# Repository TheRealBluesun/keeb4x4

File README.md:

# keeb4x4 v2

A 4×4 macropad: STM32G431, 16 MX-style keys with per-key SK6812
RGB, up to 12 Waveshare 0.85" ScreenKey display keycaps, an EC11 rotary
encoder, and a USB-C connection that streams key/encoder events to the host
as JSON. Firmware is Rust/Embassy, with a resident USB bootloader so you never
need a debug probe after the first flash.

## What's here

| Path | Contents |
| --- | --- |
| `keeb4x4.kicad_{pro,sch,pcb}` | KiCad project: schematic and 4-layer PCB (100 × 142.5 mm) |
| [`fab/`](fab/README.md) | Gerbers, BOM and CPL for JLCPCB, plus order settings and hand-solder list |
| [`FIRMWARE_NOTES.md`](FIRMWARE_NOTES.md) | Pin map, matrix polarity, encoder, LED chain — the hardware facts firmware relies on |
| [`firmware/`](firmware/README.md) | Rust/Embassy application firmware |
| [`bootloader/`](bootloader/README.md) | USB DFU bootloader, recovery, memory layout |
| [`host/`](host/README.md) | `keeb` CLI: list devices, listen to events, build and flash firmware |
| [`enclosure/`](enclosure/README.md) | 3D-printable base (STL/STEP) and its parametric source |
| [`docs/PARTS.md`](docs/PARTS.md) | What to buy beyond the assembled board: ScreenKeys, switches, encoder |
| [`docs/PROGRAMMER.md`](docs/PROGRAMMER.md) | One-time bootloader flashing with an ST-Link clone |
| `tools/pcb/` | KiCad Python scripts used while routing the LED chain and GND stitching |

## Quick start (you have a board)

> **New board?**
> 1. Buy the parts that aren't on the assembled board: [docs/PARTS.md](docs/PARTS.md) (ScreenKeys, switches, encoder, ST-Link…)
> 2. Flash the pre-built firmware once with an ST-Link: [docs/PROGRAMMER.md](docs/PROGRAMMER.md). Image on the [releases page](https://github.com/TheRealBluesun/keeb4x4/releases/latest).

Requires [rustup](https://rustup.rs). Toolchains and targets are pinned per
project and install automatically.

```sh
cargo build --manifest-path host/Cargo.toml --release --locked
host/target/release/keeb list      # should show the board
host/target/release/keeb listen    # watch key / encoder events
```

To rebuild and flash firmware over USB:

```sh
host/target/release/keeb build
host/target/release/keeb update firmware/artifacts/update/keeb-v2.kbf
```

On Linux, install the udev rules first (see
[bootloader/README.md](bootloader/README.md#host-setup)). If the application
ever stops responding, hold the encoder button while plugging in USB to enter
recovery, then run `keeb update --recovery ...`.

**A newly assembled board is blank.** It needs a one-time bootloader install
over the SWD header (J3) with a cheap ST-Link V2 clone and `probe-rs`. Start
with **[docs/PROGRAMMER.md](docs/PROGRAMMER.md)**, which covers what to buy,
wiring and troubleshooting.

## Assembly notes

JLC assembles the SMT parts on both sides. You hand-solder the 16 switches,
the EC11 encoder, and the SWD/OLED headers. Check the
part rotations in JLC's preview before you order. See
[fab/README.md](fab/README.md).

The USB VID/PID (`c0de:cafe`, plus STM32 DFU `0483:df11` in recovery) are
prototype identities, not allocated ones.

## License

- Hardware (KiCad files, `fab/`, `enclosure/`): [CERN-OHL-P-2.0](LICENSE-HARDWARE)
- Software (`firmware/`, `bootloader/`, `host/`, `tools/`): [MIT](LICENSE-MIT)

ScreenKey init values are adapted from Waveshare's MIT-licensed example; see
[firmware/THIRD_PARTY.md](firmware/THIRD_PARTY.md).

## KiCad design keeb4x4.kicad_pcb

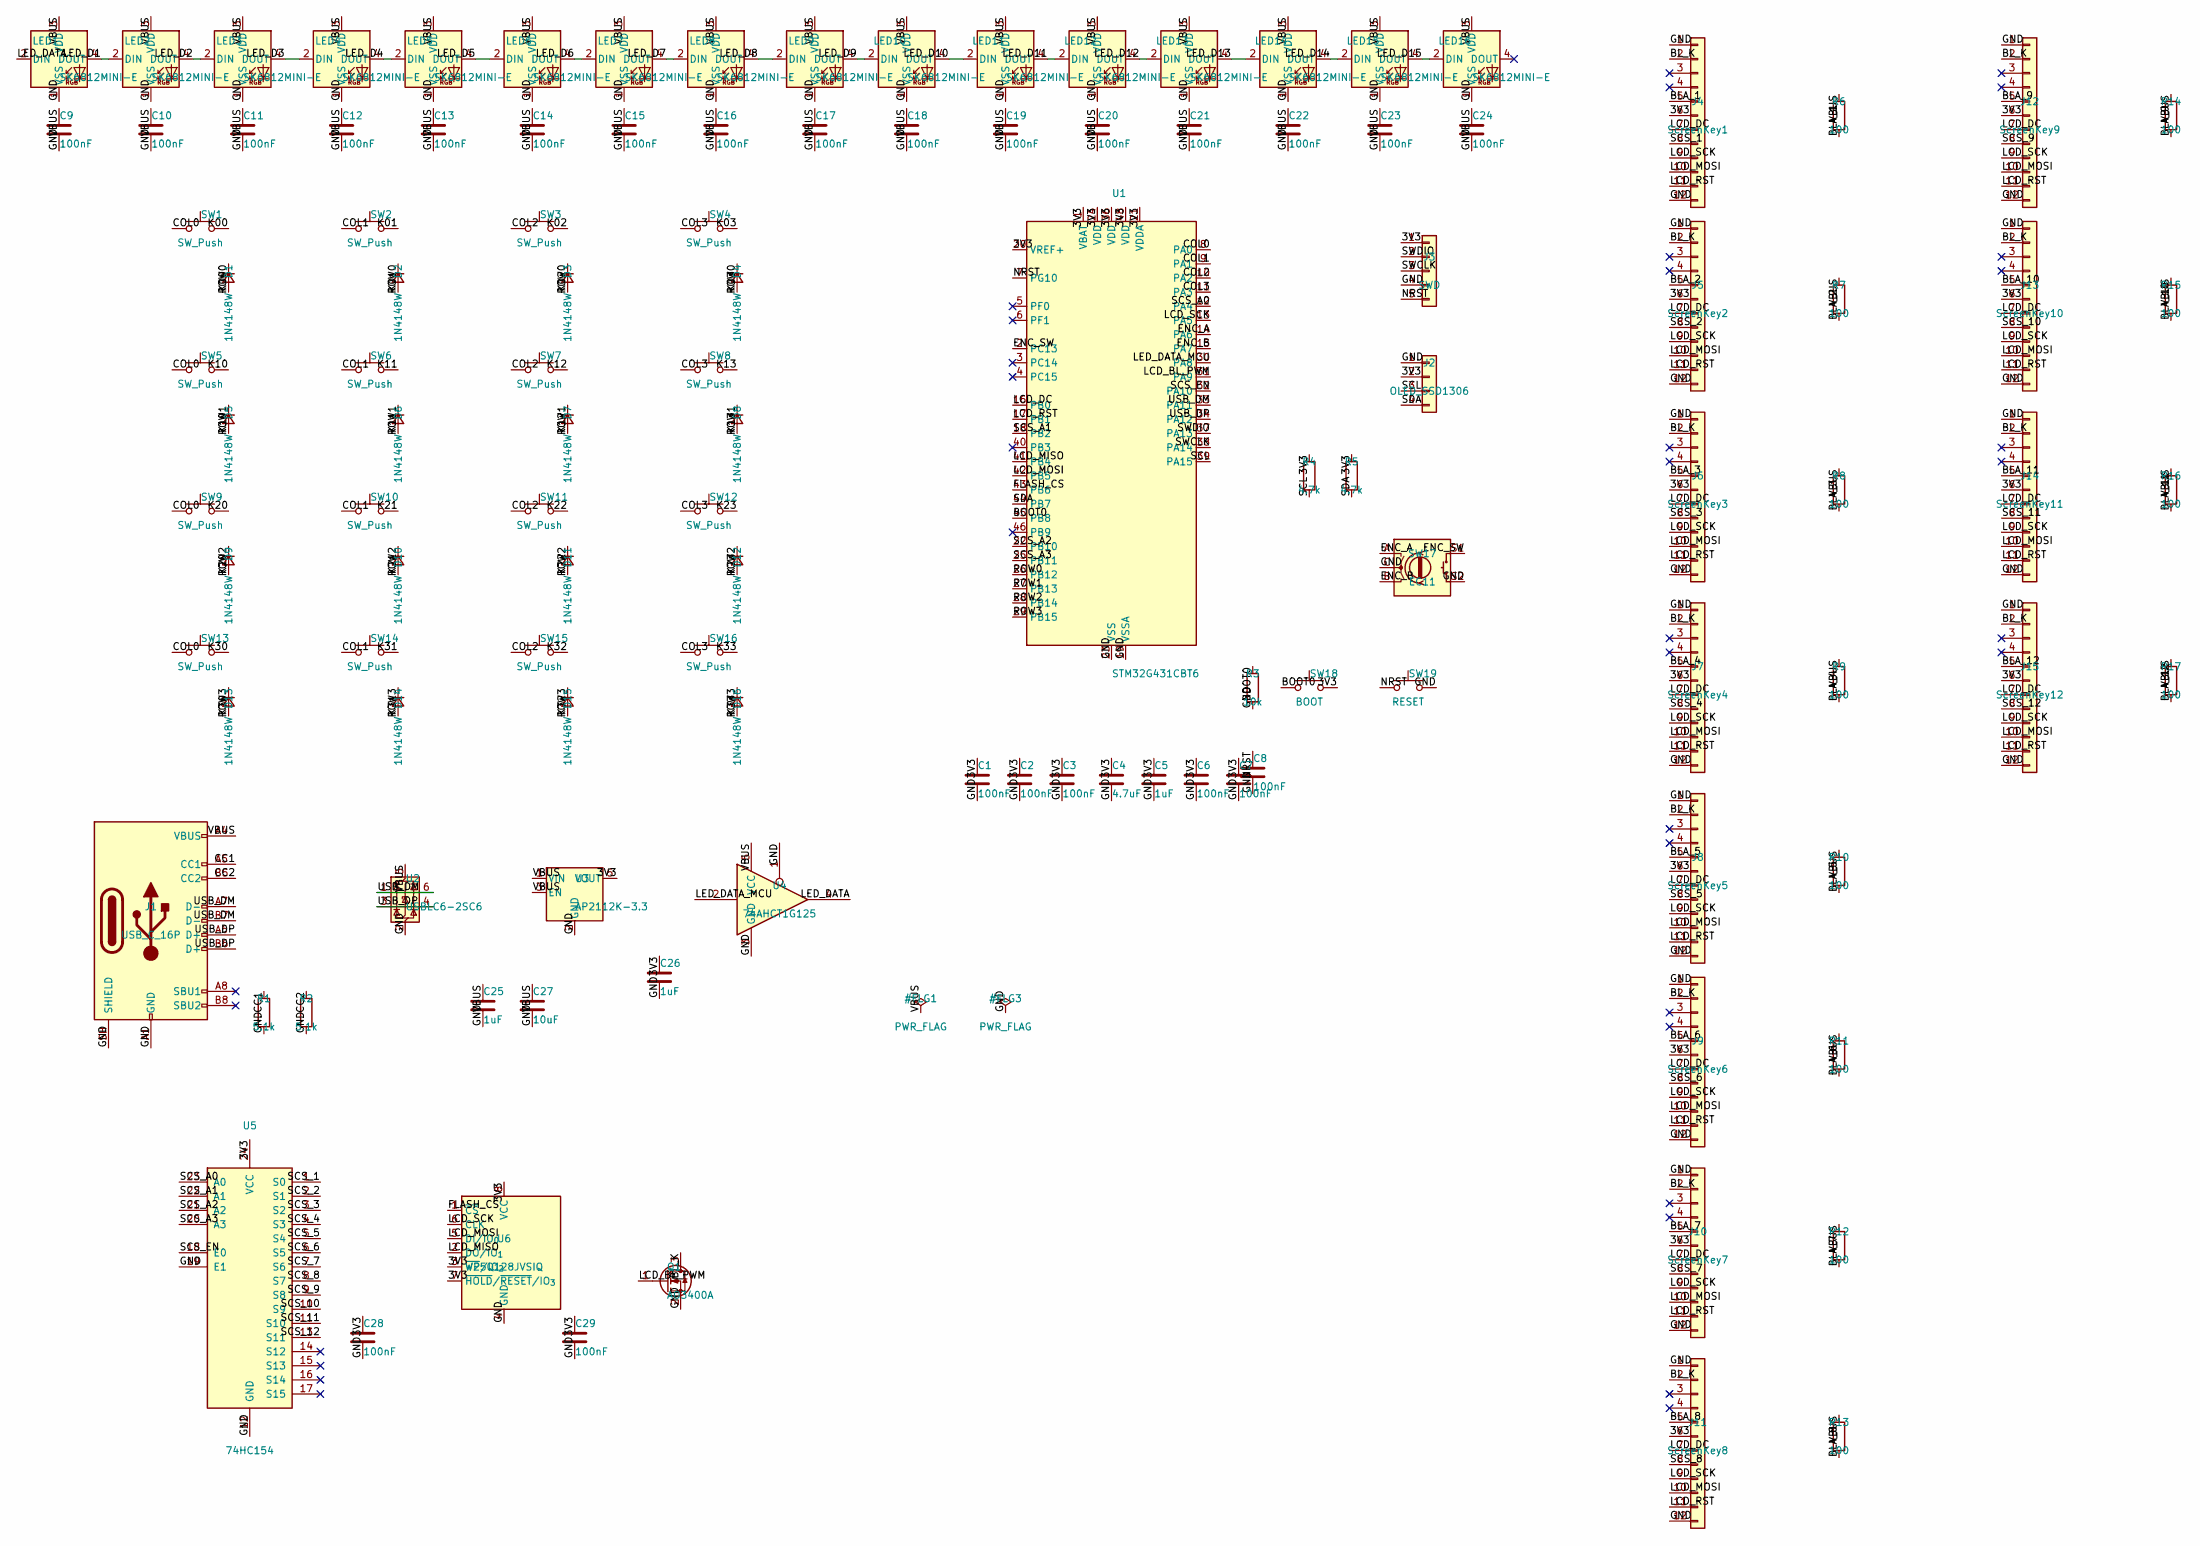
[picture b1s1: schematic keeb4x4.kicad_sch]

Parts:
C1, C2, C3, C6, C7, C8, C9, C10, C11, C12, C13, C14, C15, C16, C17, C18, C19, C20, C21, C22, C23, C24, C28, C29: 100nF; C_0603_1608Metric
C4: 4.7uF; C_0603_1608Metric
C5, C25, C26: 1uF; C_0603_1608Metric
C27: 10uF; C_0805_2012Metric
D1, D2, D3, D4, D5, D6, D7, D8, D9, D10, D11, D12, D13, D14, D15, D16: 1N4148W; D_SOD-123
J1: USB_C_16P; USB_C_Receptacle_HRO_TYPE-C-31-M-12
J2: OLED_SSD1306; PinHeader_1x04_P2.54mm_Vertical
J3: SWD; PinHeader_1x05_P2.54mm_Vertical
J4: ScreenKey1; Hirose_FH12-12S-0.5SH_1x12-1MP_P0.50mm_Horizontal
J5: ScreenKey2; Hirose_FH12-12S-0.5SH_1x12-1MP_P0.50mm_Horizontal
J6: ScreenKey3; Hirose_FH12-12S-0.5SH_1x12-1MP_P0.50mm_Horizontal
J7: ScreenKey4; Hirose_FH12-12S-0.5SH_1x12-1MP_P0.50mm_Horizontal
J8: ScreenKey5; Hirose_FH12-12S-0.5SH_1x12-1MP_P0.50mm_Horizontal
J9: ScreenKey6; Hirose_FH12-12S-0.5SH_1x12-1MP_P0.50mm_Horizontal
J10: ScreenKey7; Hirose_FH12-12S-0.5SH_1x12-1MP_P0.50mm_Horizontal
J11: ScreenKey8; Hirose_FH12-12S-0.5SH_1x12-1MP_P0.50mm_Horizontal
J12: ScreenKey9; Hirose_FH12-12S-0.5SH_1x12-1MP_P0.50mm_Horizontal
J13: ScreenKey10; Hirose_FH12-12S-0.5SH_1x12-1MP_P0.50mm_Horizontal
J14: ScreenKey11; Hirose_FH12-12S-0.5SH_1x12-1MP_P0.50mm_Horizontal
J15: ScreenKey12; Hirose_FH12-12S-0.5SH_1x12-1MP_P0.50mm_Horizontal
LED1, LED2, LED3, LED4, LED5, LED6, LED7, LED8, LED9, LED10, LED11, LED12, LED13, LED14, LED15, LED16: SK6812MINI-E; LED_SK6812MINI-E_3.2x2.8mm_P1.5mm_ReverseMount
Q1: AO3400A; SOT-23
R1, R2: 5.1k; R_0603_1608Metric
R3: 10k; R_0603_1608Metric
R4, R5: 4.7k; R_0603_1608Metric
R6, R7, R8, R9, R10, R11, R12, R13, R14, R15, R16, R17: 100; R_0603_1608Metric
SW1, SW2, SW3, SW4, SW5, SW6, SW7, SW8, SW9, SW10, SW11, SW12, SW13, SW14, SW15, SW16: SW_Push; SW_Cherry_MX_1.00u_PCB
SW17: EC11; RotaryEncoder_Alps_EC11E-Switch_Vertical_H20mm
SW18: BOOT; SW_SPST_B3U-1000P
SW19: RESET; SW_SPST_B3U-1000P
U1: STM32G431CBT6; LQFP-48_7x7mm_P0.5mm
U2: USBLC6-2SC6; SOT-23-6
U3: AP2112K-3.3; SOT-23-5
U4: 74AHCT1G125; SOT-23-5
U5: 74HC154; SOIC-24W_7.5x15.4mm_P1.27mm
U6: W25Q128JVSIQ; SOIC-8_5.3x5.3mm_P1.27mm

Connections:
3V3: C1.1, C2.1, C3.1, C4.1, C5.1, C6.1, C7.1, C26.1, C28.1, C29.1, J2.2, J3.1, J4.6, J5.6, J6.6, J7.6, J8.6, J9.6, J10.6, J11.6, J12.6, J13.6, J14.6, J15.6, R4.1, R5.1, SW18.2, U1.1 (VBAT), U1.20 (VREF+), U1.21 (VDDA), U1.24 (VDD), U1.36 (VDD), U1.48 (VDD), U3.5 (VOUT), U5.24 (VCC), U6.3 (~WP/IO_{2}), U6.7 (~HOLD/~RESET/IO_{3}), U6.8 (VCC)
BLA_1: J4.5, R6.2
BLA_2: J5.5, R7.2
BLA_3: J6.5, R8.2
BLA_4: J7.5, R9.2
BLA_5: J8.5, R10.2
BLA_6: J9.5, R11.2
BLA_7: J10.5, R12.2
BLA_8: J11.5, R13.2
BLA_9: J12.5, R14.2
BLA_10: J13.5, R15.2
BLA_11: J14.5, R16.2
BLA_12: J15.5, R17.2
BL_K: J4.2, J5.2, J6.2, J7.2, J8.2, J9.2, J10.2, J11.2, J12.2, J13.2, J14.2, J15.2, Q1.3 (D)
BOOT0: R3.1, SW18.1, U1.45 (PB8)
CC1: J1.A5 (CC1), R1.1
CC2: J1.B5 (CC2), R2.1
COL0: SW1.1, SW5.1, SW9.1, SW13.1, U1.8 (PA0)
COL1: SW2.1, SW6.1, SW10.1, SW14.1, U1.9 (PA1)
COL2: SW3.1, SW7.1, SW11.1, SW15.1, U1.10 (PA2)
COL3: SW4.1, SW8.1, SW12.1, SW16.1, U1.11 (PA3)
ENC_A: SW17.A, U1.14 (PA6)
ENC_B: SW17.B, U1.15 (PA7)
ENC_SW: SW17.S1, U1.2 (PC13)
FLASH_CS: U1.43 (PB6), U6.1 (~CS)
GND: C1.2, C2.2, C3.2, C4.2, C5.2, C6.2, C7.2, C8.2, C9.2, C10.2, C11.2, C12.2, C13.2, C14.2, C15.2, C16.2, C17.2, C18.2, C19.2, C20.2, C21.2, C22.2, C23.2, C24.2, C25.2, C26.2, C27.2, C28.2, C29.2, J1.A1 (GND), J1.A12 (GND), J1.B1 (GND), J1.B12 (GND), J1.SH (SHIELD), J2.1, J3.4, J4.1, J4.12, J5.1, J5.12, J6.1, J6.12, J7.1, J7.12, J8.1, J8.12, J9.1, J9.12, J10.1, J10.12, J11.1, J11.12, J12.1, J12.12, J13.1, J13.12, J14.1, J14.12, J15.1, J15.12, LED1.1 (VSS), LED2.1 (VSS), LED3.1 (VSS), LED4.1 (VSS), LED5.1 (VSS), LED6.1 (VSS), LED7.1 (VSS), LED8.1 (VSS), LED9.1 (VSS), LED10.1 (VSS), LED11.1 (VSS), LED12.1 (VSS), LED13.1 (VSS), LED14.1 (VSS), LED15.1 (VSS), LED16.1 (VSS), Q1.2 (S), R1.2, R2.2, R3.2, SW17.C, SW17.S2, SW19.2, U1.19 (VSSA), U1.23 (VSS), U1.35 (VSS), U1.47 (VSS), U2.2 (GND), U3.2 (GND), U4.1, U4.3 (GND), U5.12 (GND), U5.19 (E1), U6.4 (GND)
K00: D1.2 (A), SW1.2
K01: D2.2 (A), SW2.2
K02: D3.2 (A), SW3.2
K03: D4.2 (A), SW4.2
K10: D5.2 (A), SW5.2
K11: D6.2 (A), SW6.2
K12: D7.2 (A), SW7.2
K13: D8.2 (A), SW8.2
K20: D9.2 (A), SW9.2
K21: D10.2 (A), SW10.2
K22: D11.2 (A), SW11.2
K23: D12.2 (A), SW12.2
K30: D13.2 (A), SW13.2
K31: D14.2 (A), SW14.2
K32: D15.2 (A), SW15.2
K33: D16.2 (A), SW16.2
LCD_BL_PWM: Q1.1 (G), U1.31 (PA9)
LCD_DC: J4.7, J5.7, J6.7, J7.7, J8.7, J9.7, J10.7, J11.7, J12.7, J13.7, J14.7, J15.7, U1.16 (PB0)
LCD_MISO: U1.41 (PB4), U6.2 (DO/IO_{1})
LCD_MOSI: J4.10, J5.10, J6.10, J7.10, J8.10, J9.10, J10.10, J11.10, J12.10, J13.10, J14.10, J15.10, U1.42 (PB5), U6.5 (DI/IO_{0})
LCD_RST: J4.11, J5.11, J6.11, J7.11, J8.11, J9.11, J10.11, J11.11, J12.11, J13.11, J14.11, J15.11, U1.17 (PB1)
LCD_SCK: J4.9, J5.9, J6.9, J7.9, J8.9, J9.9, J10.9, J11.9, J12.9, J13.9, J14.9, J15.9, U1.13 (PA5), U6.6 (CLK)
LED_D1: LED1.4 (DOUT), LED2.2 (DIN)
LED_D2: LED2.4 (DOUT), LED3.2 (DIN)
LED_D3: LED3.4 (DOUT), LED4.2 (DIN)
LED_D4: LED4.4 (DOUT), LED5.2 (DIN)
LED_D5: LED5.4 (DOUT), LED6.2 (DIN)
LED_D6: LED6.4 (DOUT), LED7.2 (DIN)
LED_D7: LED7.4 (DOUT), LED8.2 (DIN)
LED_D8: LED8.4 (DOUT), LED9.2 (DIN)
LED_D9: LED9.4 (DOUT), LED10.2 (DIN)
LED_D10: LED10.4 (DOUT), LED11.2 (DIN)
LED_D11: LED11.4 (DOUT), LED12.2 (DIN)
LED_D12: LED12.4 (DOUT), LED13.2 (DIN)
LED_D13: LED13.4 (DOUT), LED14.2 (DIN)
LED_D14: LED14.4 (DOUT), LED15.2 (DIN)
LED_D15: LED15.4 (DOUT), LED16.2 (DIN)
LED_DATA: LED1.2 (DIN), U4.4
LED_DATA_MCU: U1.30 (PA8), U4.2
NRST: C8.1, J3.5, SW19.1, U1.7 (PG10)
ROW0: D1.1 (K), D2.1 (K), D3.1 (K), D4.1 (K), U1.26 (PB12)
ROW1: D5.1 (K), D6.1 (K), D7.1 (K), D8.1 (K), U1.27 (PB13)
ROW2: D9.1 (K), D10.1 (K), D11.1 (K), D12.1 (K), U1.28 (PB14)
ROW3: D13.1 (K), D14.1 (K), D15.1 (K), D16.1 (K), U1.29 (PB15)
SCL: J2.3, R4.2, U1.39 (PA15)
SCS_1: J4.8, U5.1 (S0)
SCS_2: J5.8, U5.2 (S1)
SCS_3: J6.8, U5.3 (S2)
SCS_4: J7.8, U5.4 (S3)
SCS_5: J8.8, U5.5 (S4)
SCS_6: J9.8, U5.6 (S5)
SCS_7: J10.8, U5.7 (S6)
SCS_8: J11.8, U5.8 (S7)
SCS_9: J12.8, U5.9 (S8)
SCS_10: J13.8, U5.10 (S9)
SCS_11: J14.8, U5.11 (S10)
SCS_12: J15.8, U5.13 (S11)
SCS_13: U5.14 (S12)
SCS_14: U5.15 (S13)
SCS_15: U5.16 (S14)
SCS_16: U5.17 (S15)
SCS_A0: U1.12 (PA4), U5.23 (A0)
SCS_A1: U1.18 (PB2), U5.22 (A1)
SCS_A2: U1.22 (PB10), U5.21 (A2)
SCS_A3: U1.25 (PB11), U5.20 (A3)
SCS_EN: U1.32 (PA10), U5.18 (E0)
SDA: J2.4, R5.2, U1.44 (PB7)
SWCLK: J3.3, U1.38 (PA14)
SWDIO: J3.2, U1.37 (PA13)
USB_DM: J1.A7 (D-), J1.B7 (D-), U1.33 (PA11), U2.1 (I/O1), U2.6 (I/O1)
USB_DP: J1.A6 (D+), J1.B6 (D+), U1.34 (PA12), U2.3 (I/O2), U2.4 (I/O2)
VBUS: C9.1, C10.1, C11.1, C12.1, C13.1, C14.1, C15.1, C16.1, C17.1, C18.1, C19.1, C20.1, C21.1, C22.1, C23.1, C24.1, C25.1, C27.1, J1.A4 (VBUS), J1.A9 (VBUS), J1.B4 (VBUS), J1.B9 (VBUS), LED1.3 (VDD), LED2.3 (VDD), LED3.3 (VDD), LED4.3 (VDD), LED5.3 (VDD), LED6.3 (VDD), LED7.3 (VDD), LED8.3 (VDD), LED9.3 (VDD), LED10.3 (VDD), LED11.3 (VDD), LED12.3 (VDD), LED13.3 (VDD), LED14.3 (VDD), LED15.3 (VDD), LED16.3 (VDD), R6.1, R7.1, R8.1, R9.1, R10.1, R11.1, R12.1, R13.1, R14.1, R15.1, R16.1, R17.1, U2.5 (VBUS), U3.1 (VIN), U3.3 (EN), U4.5 (VCC)

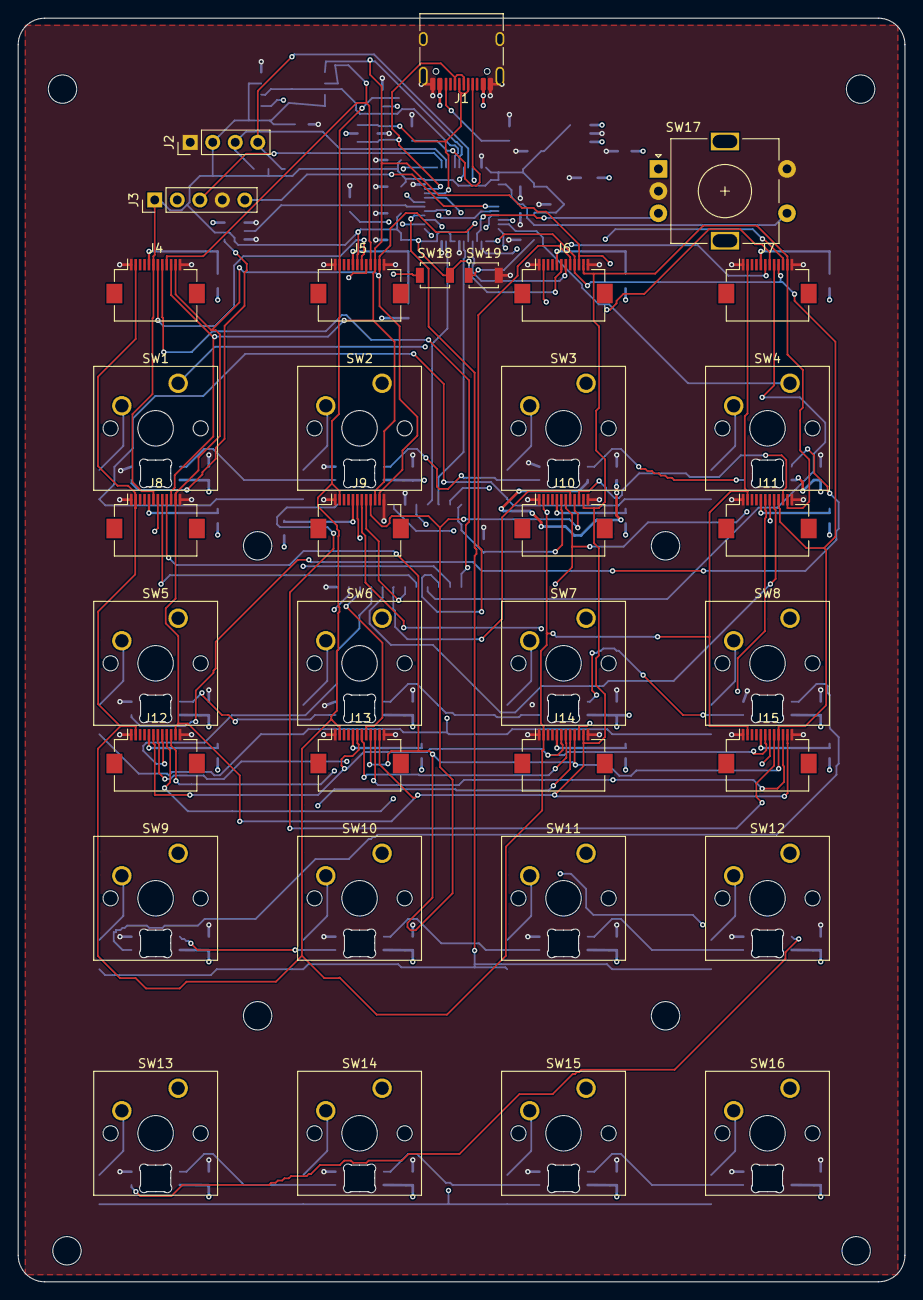
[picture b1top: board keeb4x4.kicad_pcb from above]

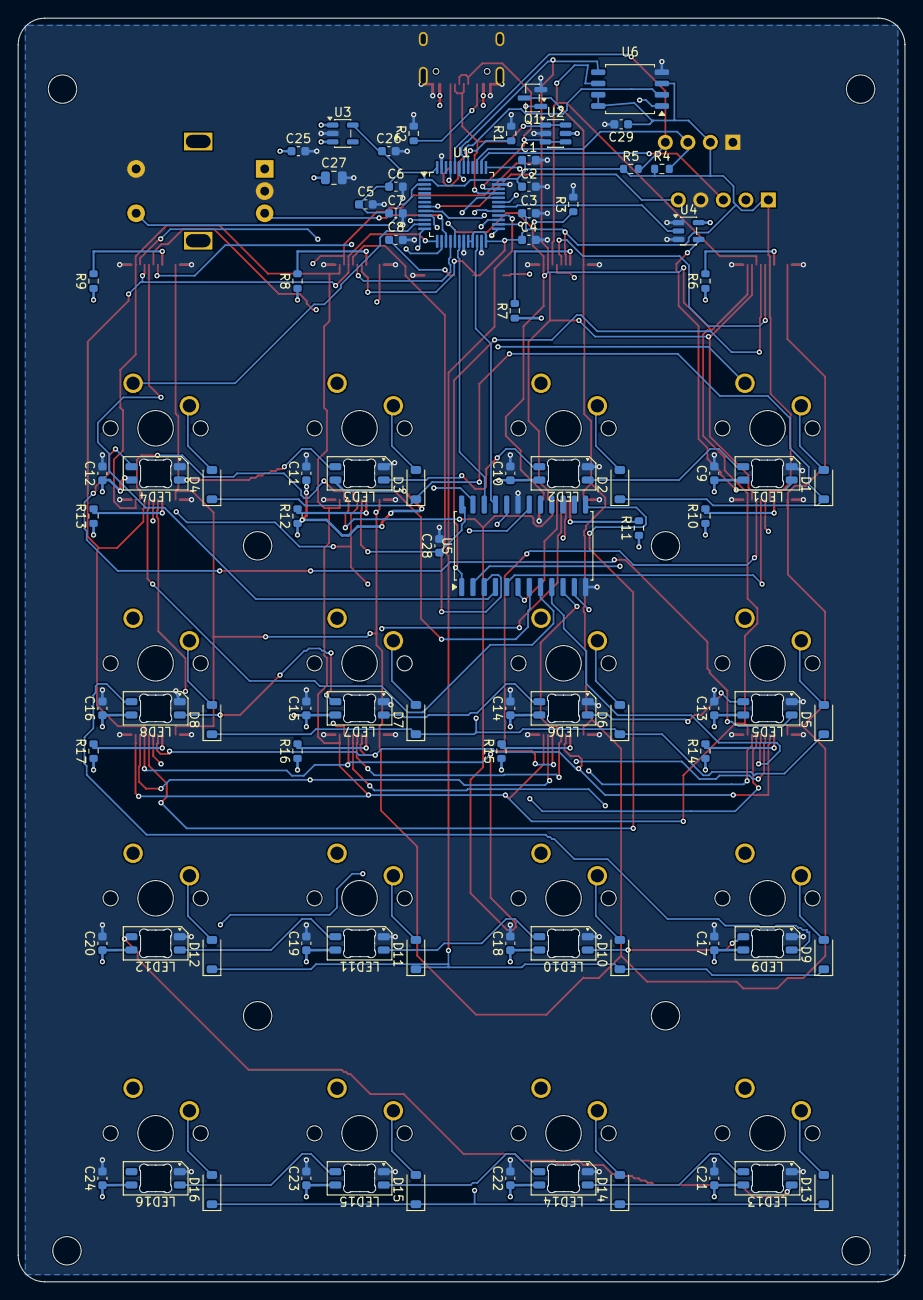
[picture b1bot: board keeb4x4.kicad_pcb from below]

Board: 4 copper layers, 100.0 x 142.5 mm, 127 parts (85 on the bottom side), 94 nets.

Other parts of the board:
H1, H2, H3, H4, H5, H6, H7, H8: MountingHole_3.2mm_M3

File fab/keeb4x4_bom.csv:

Comment,Designator,Footprint,LCSC Part #,Quantity
100nF,"C1,C2,C3,C6,C7,C8,C9,C10,C11,C12,C13,C14,C15,C16,C17,C18,C19,C20,C21,C22,C23,C24,C28,C29",C_0603_1608Metric,C14663,24
4.7uF,C4,C_0603_1608Metric,C19666,1
1uF,"C5,C25,C26",C_0603_1608Metric,C15849,3
10uF,C27,C_0805_2012Metric,C15850,1
1N4148W,"D1,D2,D3,D4,D5,D6,D7,D8,D9,D10,D11,D12,D13,D14,D15,D16",D_SOD-123,C81598,16
USB_C_16P,J1,USB_C_Receptacle_HRO_TYPE-C-31-M-12,C165948,1
FH12-12S-0.5SH (ScreenKey FPC),"J4,J5,J6,J7,J8,J9,J10,J11,J12,J13,J14,J15",Hirose_FH12-12S-0.5SH_1x12-1MP_P0.50mm_Horizontal,C88360,12
SK6812MINI-E,"LED1,LED2,LED3,LED4,LED5,LED6,LED7,LED8,LED9,LED10,LED11,LED12,LED13,LED14,LED15,LED16",LED_SK6812MINI-E_3.2x2.8mm_P1.5mm_ReverseMount,C5149201,16
AO3400A,Q1,SOT-23,C20917,1
5.1k,"R1,R2",R_0603_1608Metric,C23186,2
10k,R3,R_0603_1608Metric,C25804,1
4.7k,"R4,R5",R_0603_1608Metric,C23162,2
100,"R6,R7,R8,R9,R10,R11,R12,R13,R14,R15,R16,R17",R_0603_1608Metric,C22775,12
B3U-1000P tactile,"SW18,SW19",SW_SPST_B3U-1000P,C231329,2
STM32G431CBT6,U1,LQFP-48_7x7mm_P0.5mm,C529355,1
USBLC6-2SC6,U2,SOT-23-6,C2687116,1
AP2112K-3.3,U3,SOT-23-5,C51118,1
74AHCT1G125,U4,SOT-23-5,C7484,1
74HC154,U5,SOIC-24W_7.5x15.4mm_P1.27mm,C2832236,1
W25Q128JVSIQ,U6,SOIC-8_5.3x5.3mm_P1.27mm,C97521,1

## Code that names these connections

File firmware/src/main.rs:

#![no_std]
#![no_main]

use defmt::{info, unwrap, warn};
use embassy_executor::Spawner;
use embassy_stm32::{
    bind_interrupts, dma,
    gpio::{Input, Level, Output, Pull, Speed},
    peripherals,
    spi::{self, Spi},
    time::Hertz,
};
use embassy_time::{Duration, Instant, Ticker, Timer};
use {defmt_rtt as _, panic_probe as _};

mod boot;
mod encoder;
mod rgb;
mod screens;
mod usb;

bind_interrupts!(struct SpiIrqs {
    DMA1_CHANNEL2 => dma::InterruptHandler<peripherals::DMA1_CH2>;
    DMA1_CHANNEL3 => dma::InterruptHandler<peripherals::DMA1_CH3>;
});

#[embassy_executor::task]
async fn heartbeat() {
    let mut ticker = Ticker::every(Duration::from_secs(1));
    loop {
        info!("alive: uptime={}s", Instant::now().as_secs());
        ticker.next().await;
    }
}

#[embassy_executor::main]
async fn main(spawner: Spawner) {
    // Default clocks use the internal 16 MHz HSI; the board has no crystal.
    let mut config = embassy_stm32::Config::default();
    config.rcc.hsi48 = Some(embassy_stm32::rcc::Hsi48Config {
        sync_from_usb: true,
    });
    config.rcc.mux.clk48sel = embassy_stm32::rcc::mux::Clk48sel::HSI48;
    let p = embassy_stm32::init(config);
    spawner.spawn(unwrap!(usb::run(p.USB, p.PA12, p.PA11)));

    // Deselect everything before enabling SPI. Keep these GPIO owners alive.
    let screen_enable = Output::new(p.PA10, Level::High, Speed::Low);
    let mut flash_cs = Output::new(p.PB6, Level::High, Speed::Low);
    let screen_address = [
        Output::new(p.PA4, Level::Low, Speed::Low),
        Output::new(p.PB2, Level::Low, Speed::Low),
        Output::new(p.PB10, Level::Low, Speed::Low),
        Output::new(p.PB11, Level::Low, Speed::Low),
    ];
    let screen_dc = Output::new(p.PB0, Level::Low, Speed::Low);
    let screen_reset = Output::new(p.PB1, Level::Low, Speed::Low);
    let mut leds = rgb::Leds::new(p.TIM1, p.PA8, p.DMA1_CH1);
    let mut pixels = [rgb::Rgb::default(); rgb::LED_COUNT];
    leds.write(&pixels).await;

    info!("Hello world! keeb-v2 STM32G431CB / Embassy");
    info!("USB CDC event stream enabled; starting displays and input tasks");
    spawner.spawn(unwrap!(heartbeat()));
    spawner.spawn(unwrap!(encoder::run(p.TIM3, p.PA6, p.PA7, p.PC13)));

    let mut config = spi::Config::default();
    config.frequency = Hertz(4_000_000);
    let mut spi = Spi::new(
        p.SPI1, p.PA5, p.PB5, p.PB4, p.DMA1_CH2, p.DMA1_CH3, SpiIrqs, config,
    );
    // Read-only JEDEC identity check. The screen decoder stays disabled.
    Timer::after_millis(10).await;
    let mut id = [0x9f_u8, 0, 0, 0];
    flash_cs.set_low();
    let result = spi.blocking_transfer_in_place(&mut id);
    flash_cs.set_high();
    match result {
        Ok(()) => {
            info!("SPI flash JEDEC ID: {=[u8]:x}", &id[1..]);
            if id[1..] != [0xef, 0x40, 0x18] {
                warn!("Expected W25Q128 ID ef 40 18; check population/wiring");
            }
        }
        Err(e) => warn!("SPI flash read failed: {}", e),
    }

    spawner.spawn(unwrap!(screens::run(
        screens::Screens {
            spi,
            enable: screen_enable,
            address: screen_address,
            dc: screen_dc,
            reset: screen_reset,
            flash_cs,
        },
        p.TIM2,
        p.PA9
    )));

    // COL2ROW diodes require active-high columns and pull-down rows.
    let mut cols = [
        Output::new(p.PA0, Level::Low, Speed::Low),
        Output::new(p.PA1, Level::Low, Speed::Low),
        Output::new(p.PA2, Level::Low, Speed::Low),
        Output::new(p.PA3, Level::Low, Speed::Low),
    ];
    let rows = [
        Input::new(p.PB12, Pull::Down),
        Input::new(p.PB13, Pull::Down),
        Input::new(p.PB14, Pull::Down),
        Input::new(p.PB15, Pull::Down),
    ];
    let mut stable = [false; 16];
    let mut candidate = [false; 16];
    let mut changed_at = [Instant::now(); 16];
    let mut ticker = Ticker::every(Duration::from_millis(1));
    info!("Matrix ready: top row SW1..SW4; press keys to see events");
    loop {
        let mut leds_changed = false;
        for (col, output) in cols.iter_mut().enumerate() {
            output.set_high();
            Timer::after_micros(10).await;
            for (row, input) in rows.iter().enumerate() {
                let key = row * 4 + col;
                let pressed = input.is_high();
                let now = Instant::now();
                if candidate[key] != pressed {
                    candidate[key] = pressed;
                    changed_at[key] = now;
                }
                if stable[key] != pressed && now - changed_at[key] >= Duration::from_millis(5) {
                    stable[key] = pressed;
                    usb::key(key as u8, pressed);
                    pixels[key] = if pressed {
                        rgb::Rgb {
                            r: 255,
                            g: 255,
                            b: 255,
                        }
                    } else {
                        rgb::Rgb::default()
                    };
                    leds_changed = true;
                    info!("SW{} row={} col={} pressed={}", key + 1, row, col, pressed);
                }
            }
            output.set_low();
        }
        if leds_changed {
            leds.write(&pixels).await;
        }
        ticker.next().await;
    }
}
